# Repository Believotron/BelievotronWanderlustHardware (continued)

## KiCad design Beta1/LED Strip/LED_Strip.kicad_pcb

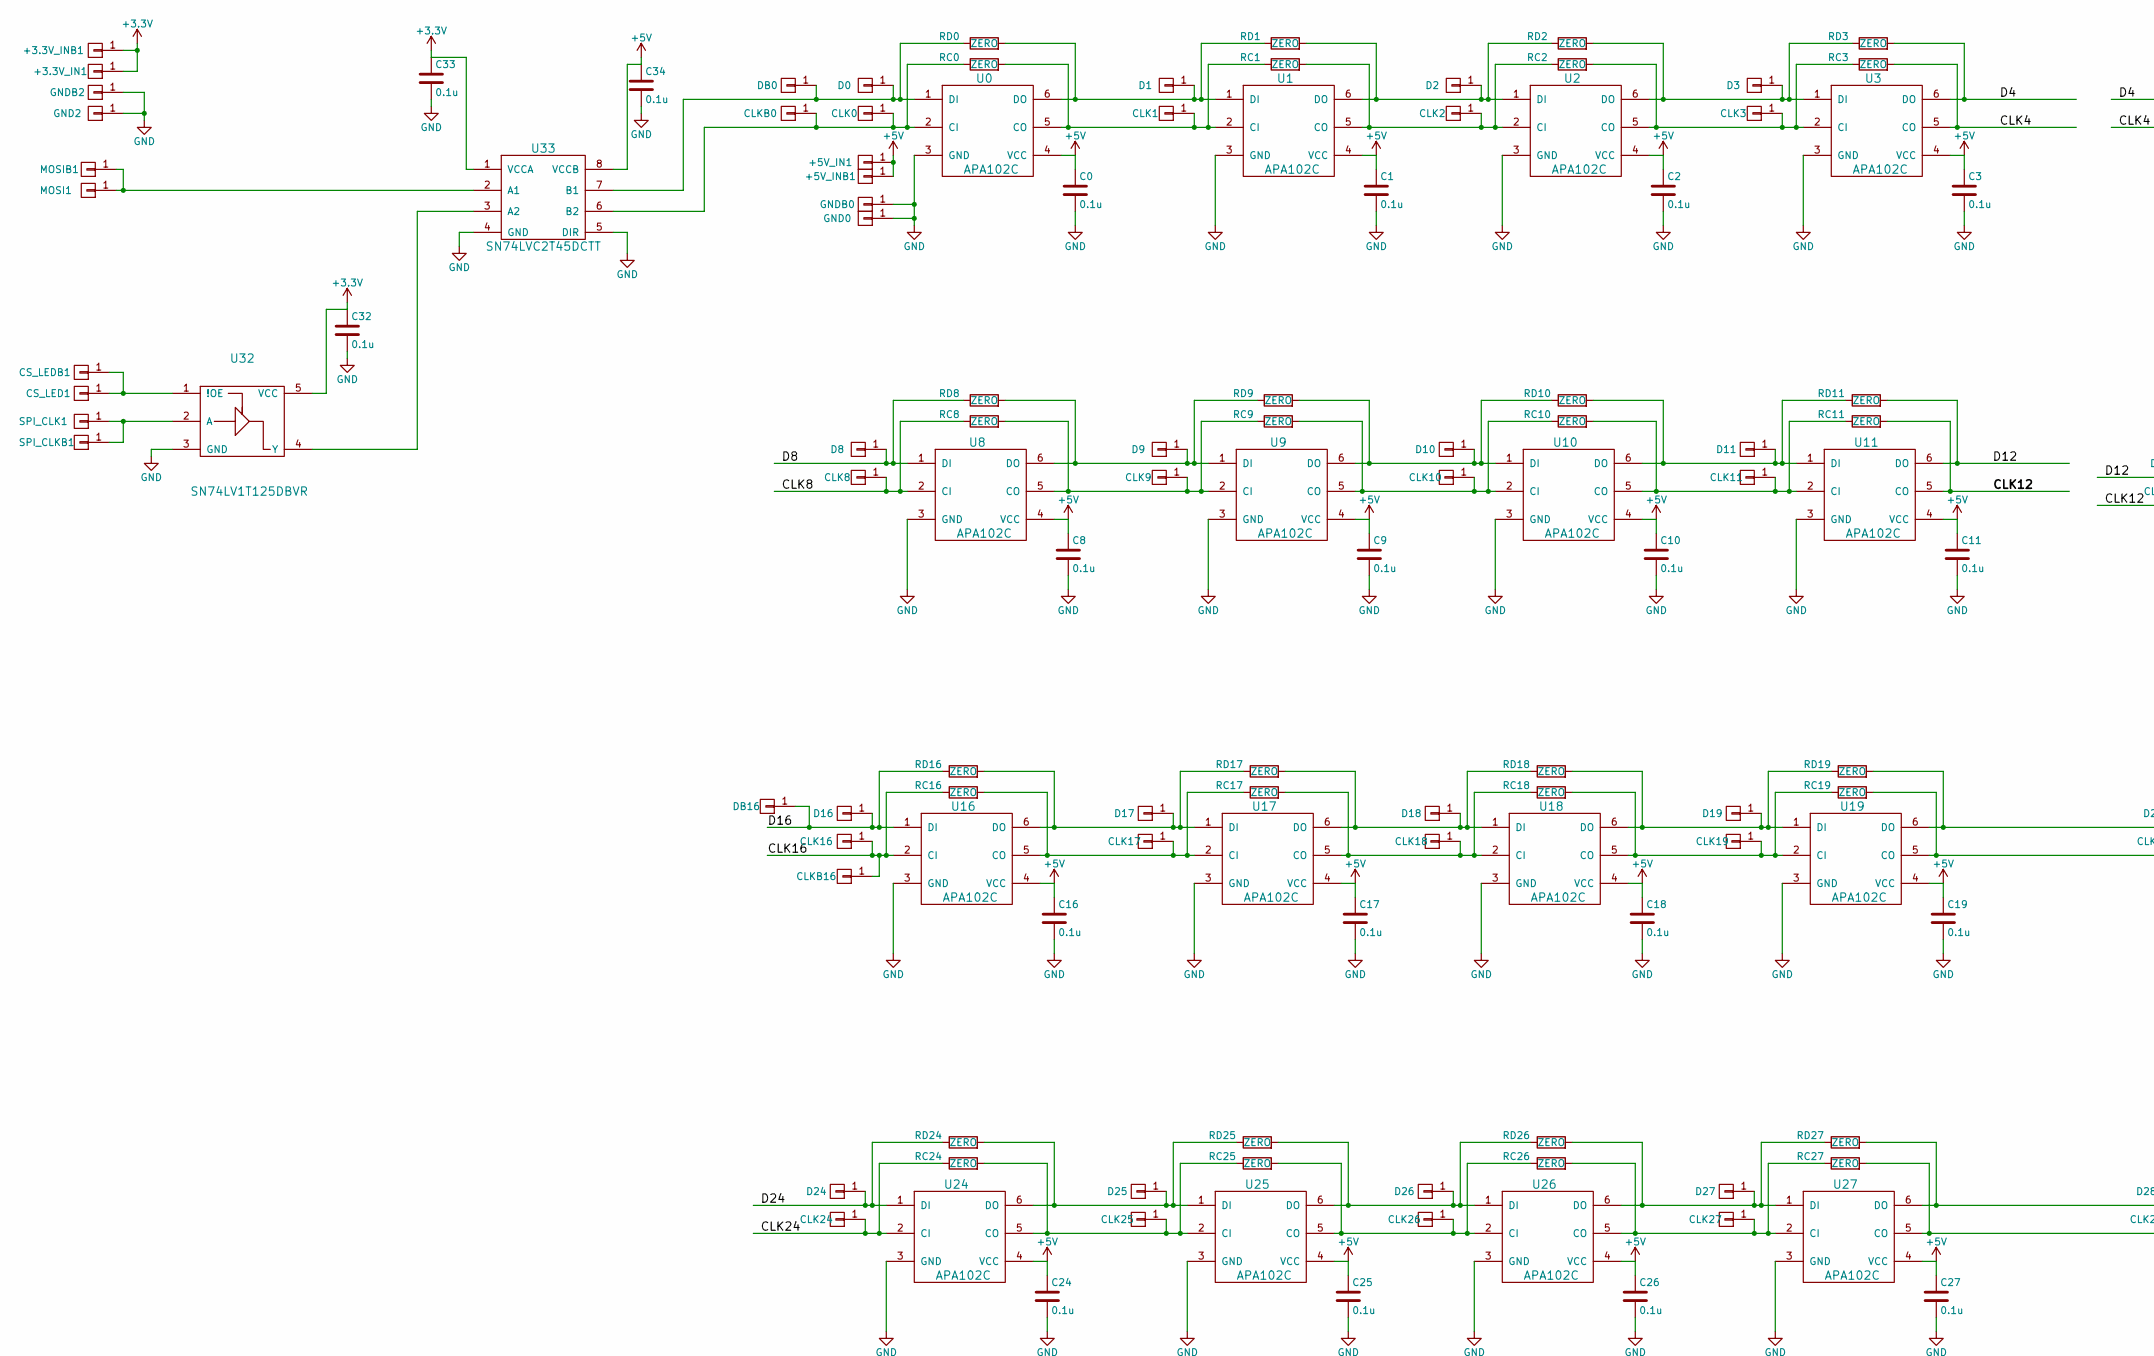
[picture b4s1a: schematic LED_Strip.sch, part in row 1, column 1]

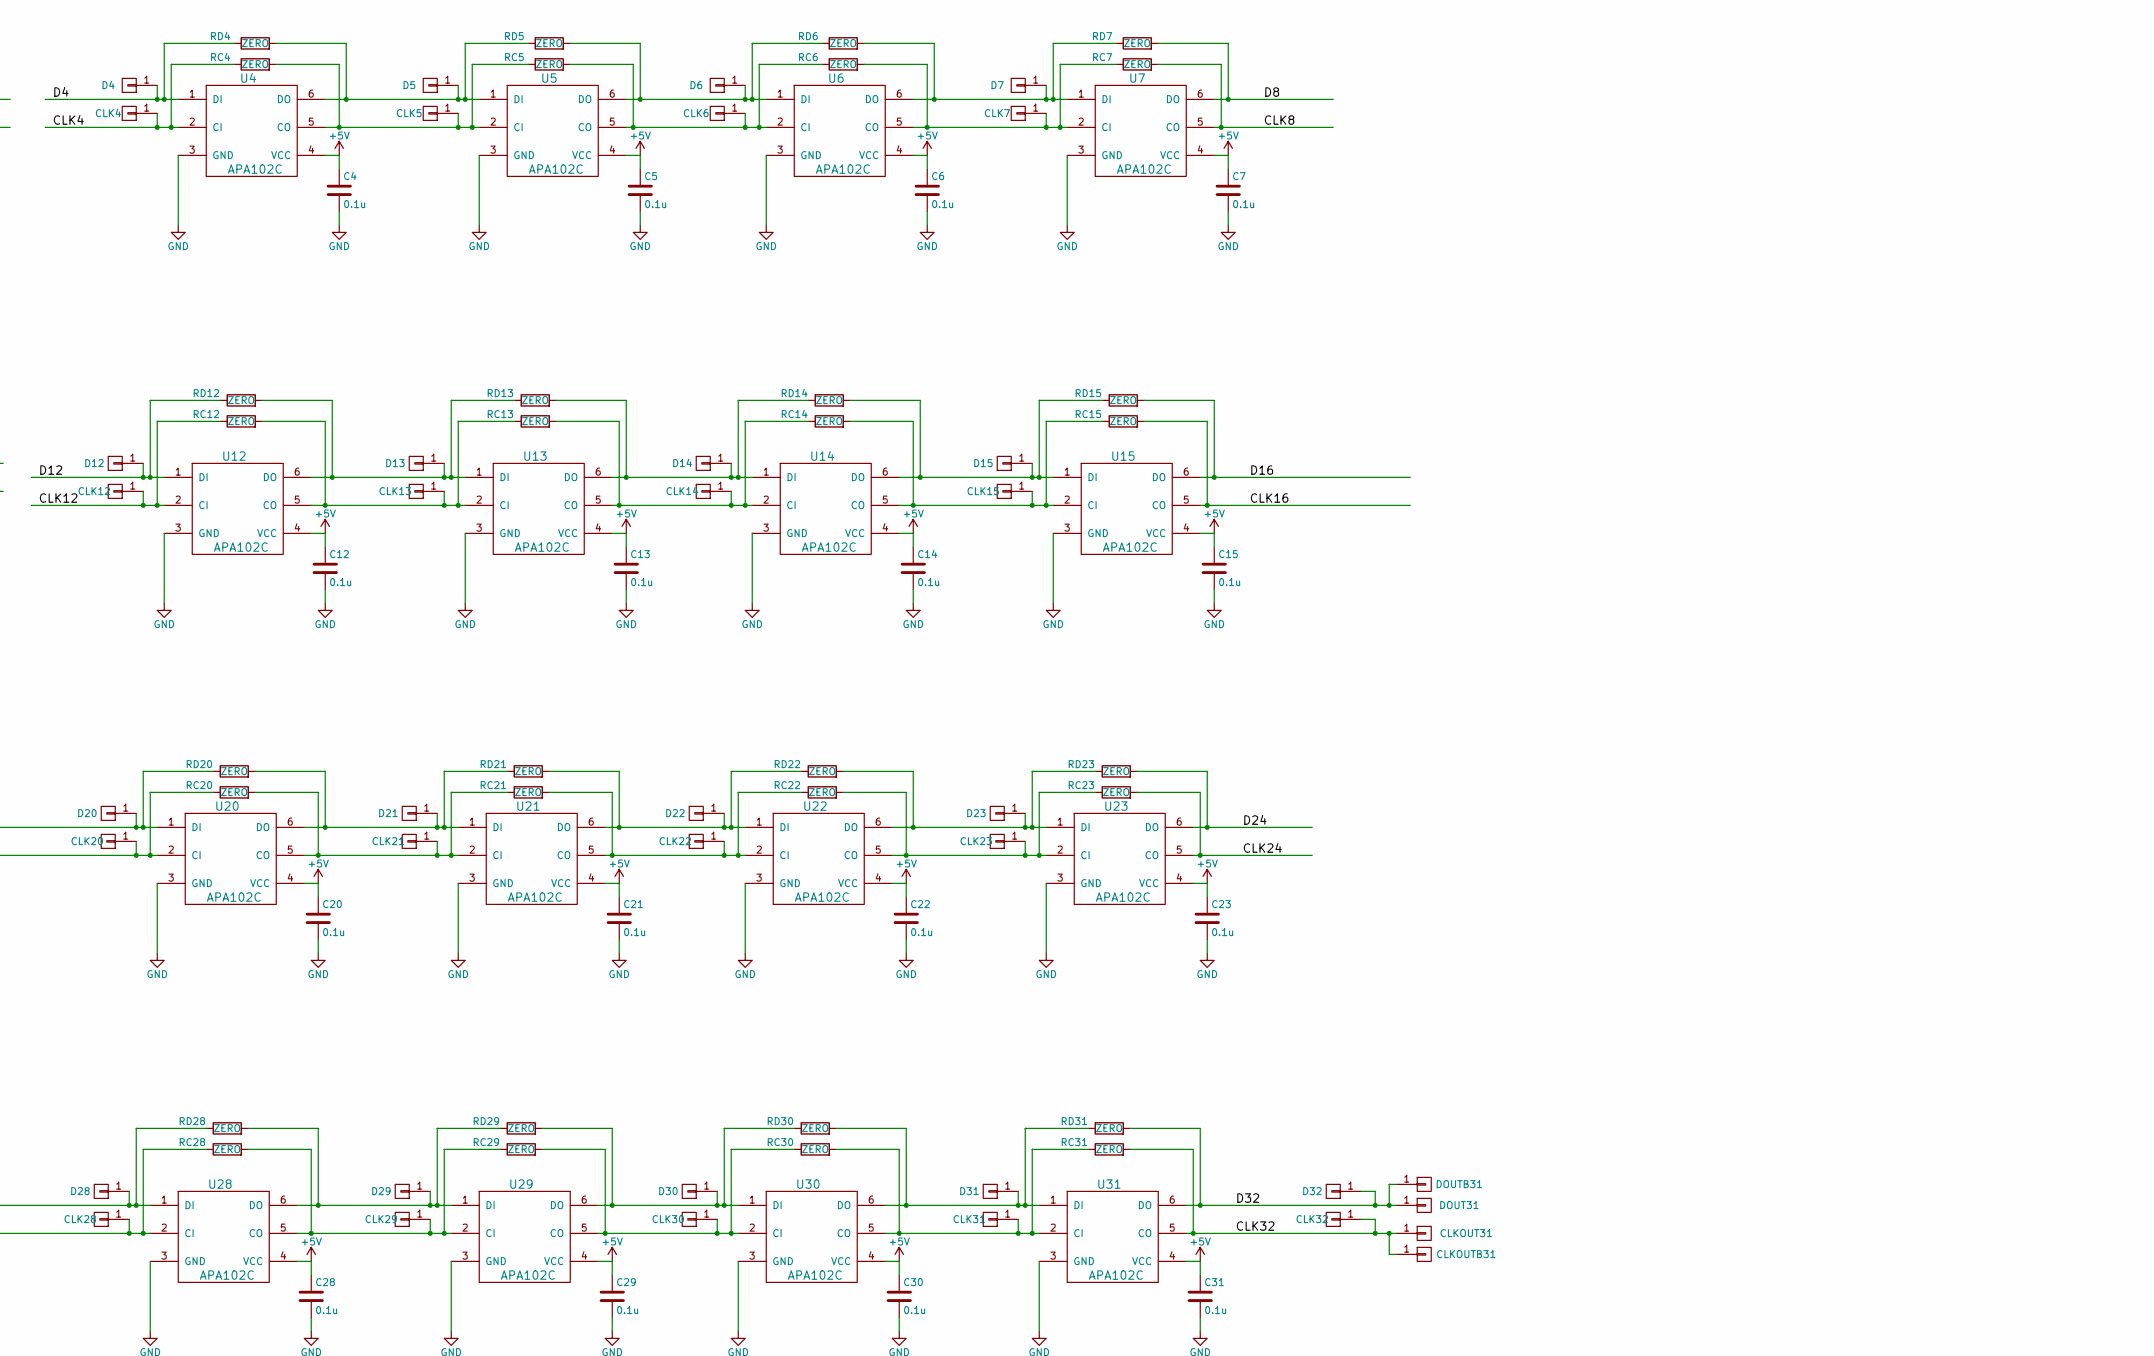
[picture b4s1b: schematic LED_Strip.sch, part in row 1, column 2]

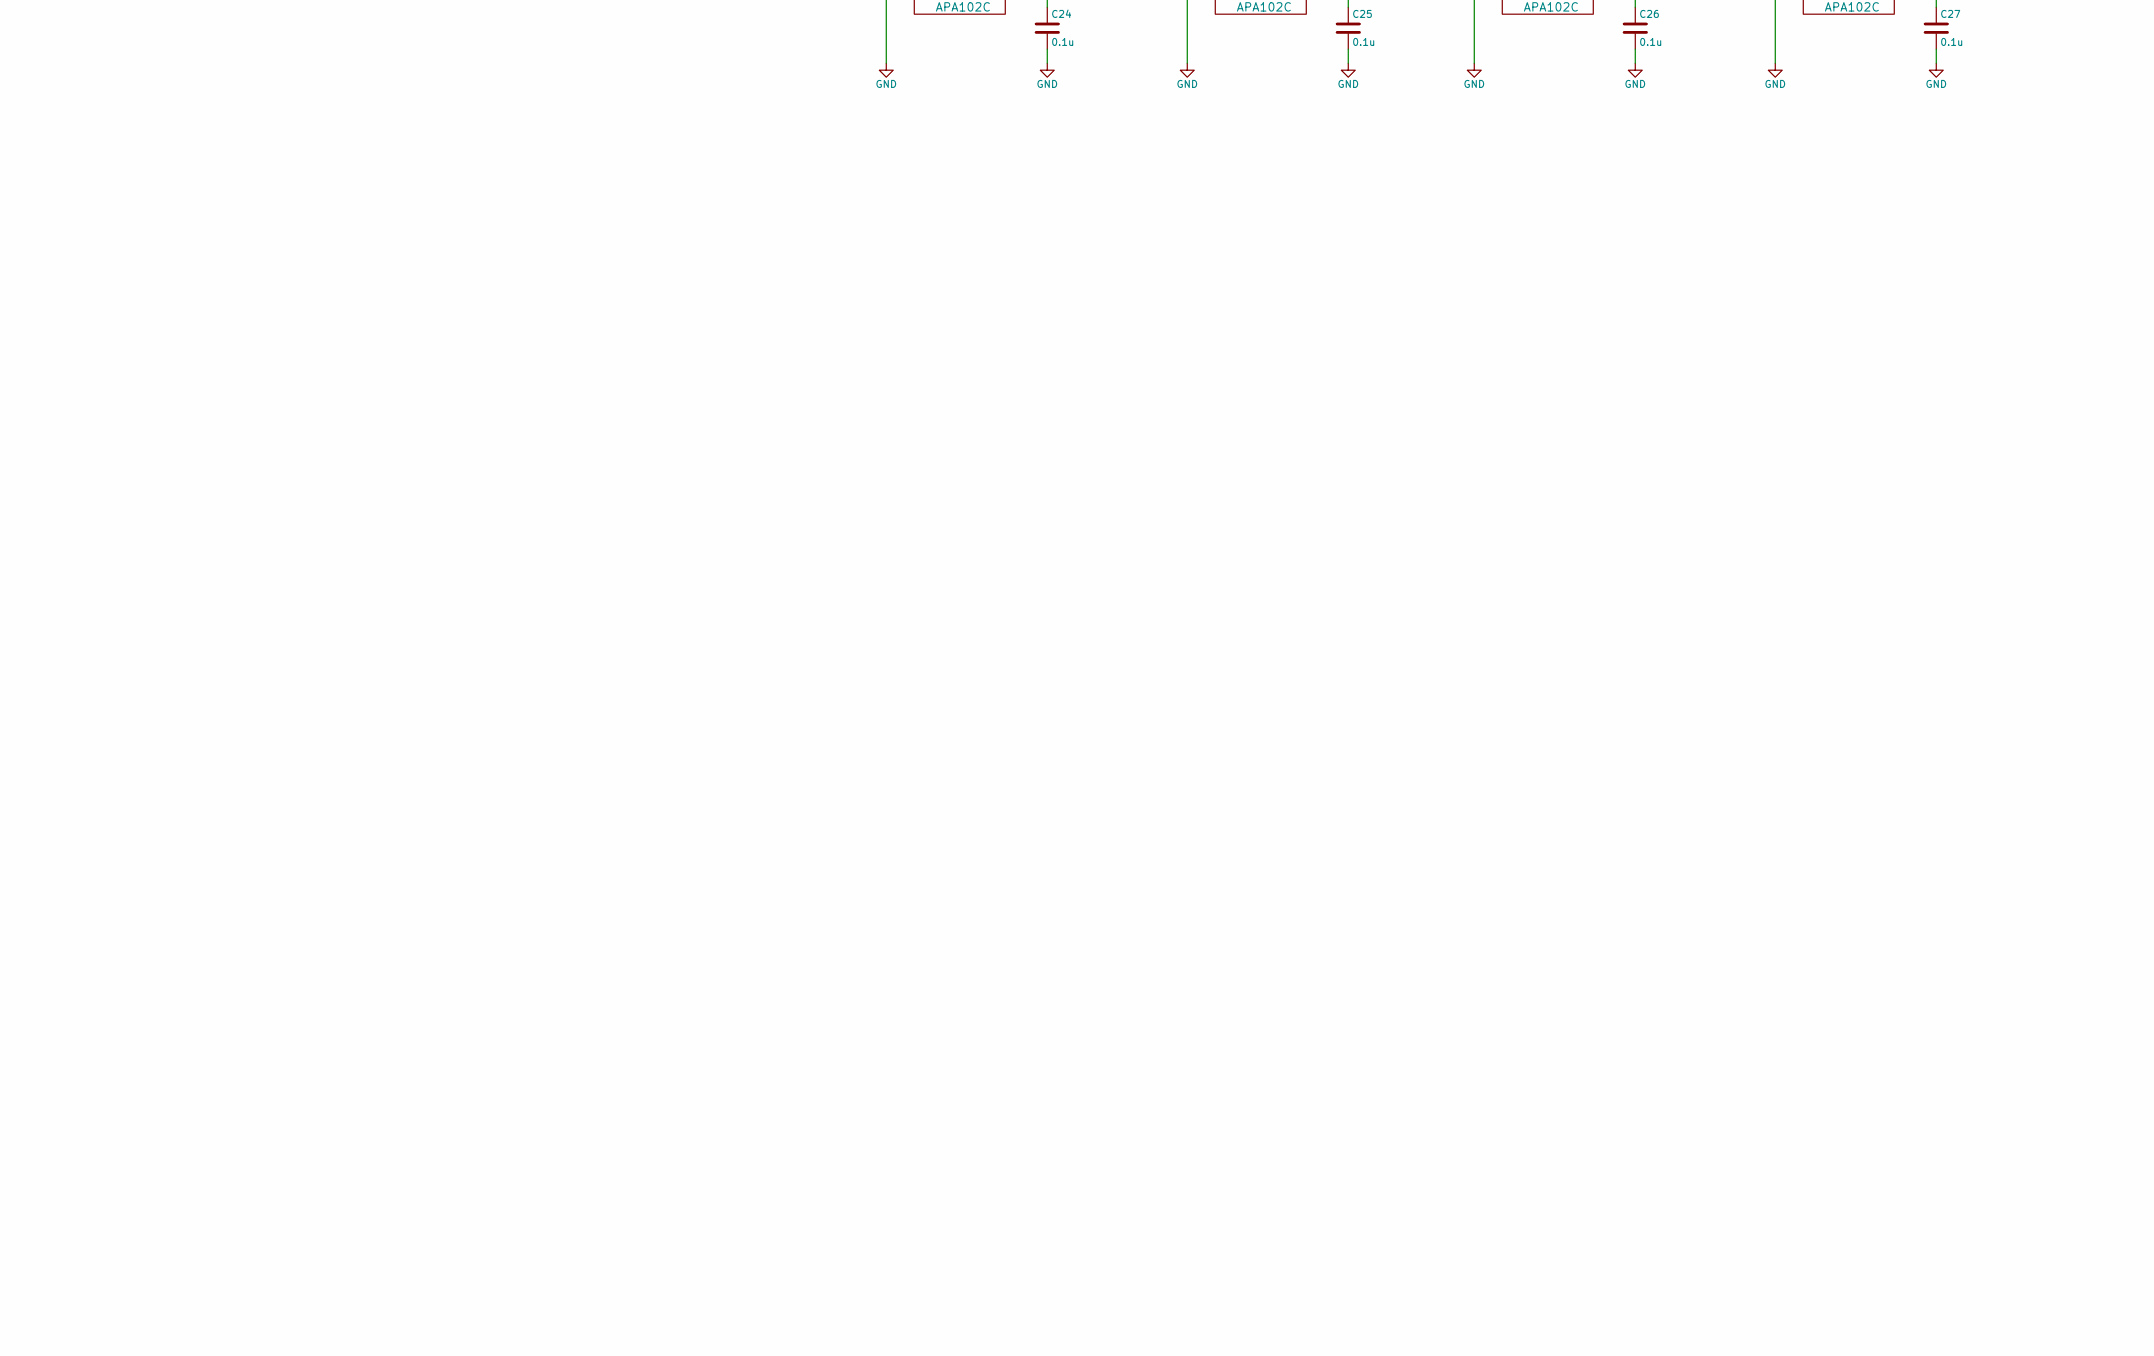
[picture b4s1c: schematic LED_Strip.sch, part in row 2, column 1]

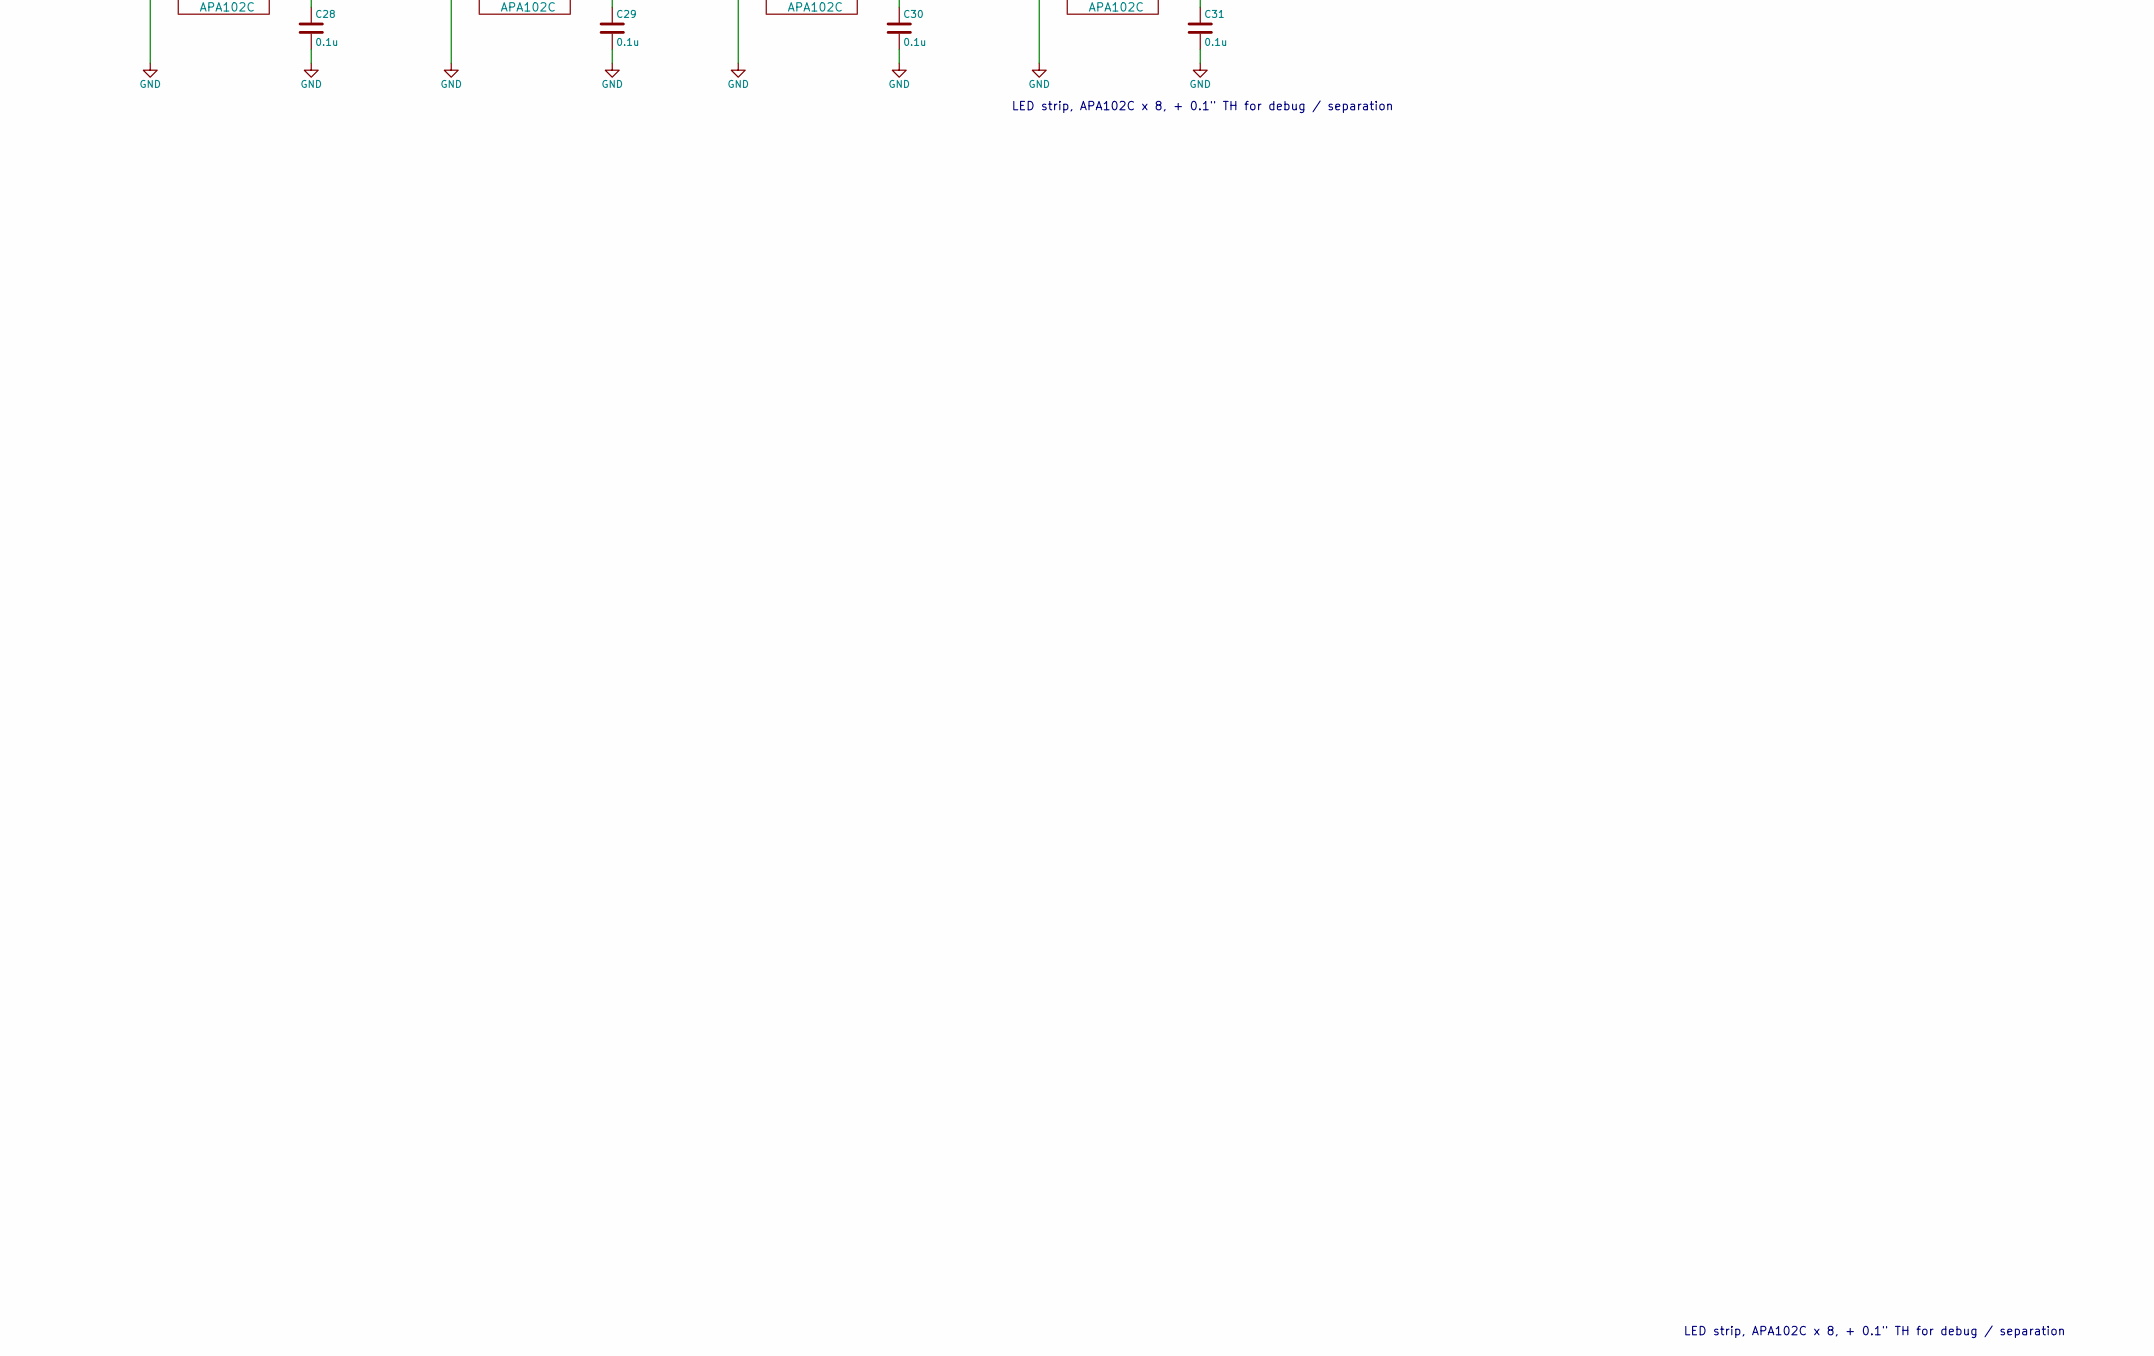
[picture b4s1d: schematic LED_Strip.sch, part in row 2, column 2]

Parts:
+3.3V_IN1, +3.3V_INB1, +5V_IN1, +5V_INB1: CONN_01X01; single_0.1; MPN ON_PCB
C0, C1, C2, C3, C4, C5, C6, C7, C8, C9, C10, C11, C12, C13, C14, C15, C16, C17, C18, C19, C20, C21, C22, C23, C24, C25, C26, C27, C28, C29, C30, C31, C32, C33, C34: 0.1u; C_0603; MPN CC0603KRX7R9BB104
CLK0, CLK16: CONN_01X01; single_0.1; MPN ON_PCB
CLK1, CLK2, CLK3, CLK4, CLK5, CLK6, CLK7, CLK8, CLK9, CLK10, CLK11, CLK12, CLK13, CLK14, CLK15, CLK17, CLK18, CLK19, CLK20, CLK21, CLK22, CLK23, CLK24, CLK25, CLK26, CLK27, CLK28, CLK29, CLK30, CLK31, CLK32: CONN_01X01; TESTPAD; MPN ON_PCB
CLKB0, CLKB16: CONN_01X01; single_0.1; MPN ON_PCB
CLKOUT31: CONN_01X01; single_0.1; MPN ON_PCB
CLKOUTB31: CONN_01X01; single_0.1; MPN ON_PCB
CS_LED1: CONN_01X01; single_0.1; MPN ON_PCB
CS_LEDB1: CONN_01X01; single_0.1; MPN ON_PCB
D0, D16: CONN_01X01; single_0.1; MPN ON_PCB
D1, D2, D3, D4, D5, D6, D7, D8, D9, D10, D11, D12, D13, D14, D15, D17, D18, D19, D20, D21, D22, D23, D24, D25, D26, D27, D28, D29, D30, D31, D32: CONN_01X01; TESTPAD; MPN ON_PCB
DB0, DB16: CONN_01X01; single_0.1; MPN ON_PCB
DOUT31: CONN_01X01; single_0.1; MPN ON_PCB
DOUTB31: CONN_01X01; single_0.1; MPN ON_PCB
GND0, GND2: CONN_01X01; single_0.1; MPN ON_PCB
GNDB0, GNDB2: CONN_01X01; single_0.1; MPN ON_PCB
MOSI1: CONN_01X01; single_0.1; MPN ON_PCB
MOSIB1: CONN_01X01; single_0.1; MPN ON_PCB
RC0, RC1, RC2, RC3, RC4, RC5, RC6, RC7, RC8, RC9, RC10, RC11, RC12, RC13, RC14, RC15, RC16, RC17, RC18, RC19, RC20, RC21, RC22, RC23, RC24, RC25, RC26, RC27, RC28, RC29, RC30, RC31: ZERO; R_0603; MPN CRCW06030000Z0EA
RD0, RD1, RD2, RD3, RD4, RD5, RD6, RD7, RD8, RD9, RD10, RD11, RD12, RD13, RD14, RD15, RD16, RD17, RD18, RD19, RD20, RD21, RD22, RD23, RD24, RD25, RD26, RD27, RD28, RD29, RD30, RD31: ZERO; R_0603; MPN CRCW06030000Z0EA
SPI_CLK1: CONN_01X01; single_0.1; MPN ON_PCB
SPI_CLKB1: CONN_01X01; single_0.1; MPN ON_PCB
U0, U1, U2, U3, U4, U5, U6, U7, U8, U9, U10, U11, U12, U13, U14, U15, U16, U17, U18, U19, U20, U21, U22, U23, U24, U25, U26, U27, U28, U29, U30, U31: APA102C; PLCC6-1.6x4.2_LED; MPN APA102C
U32: SN74LV1T125DBVR; SOT23-5; MPN SN74LV1T125DBVR
U33: SN74LVC2T45DCTT; SSOP8; MPN SN74LVC2T45DCTT

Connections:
+3V3: +3.3V_IN1.1, +3.3V_INB1.1, C32.1, C33.1, U32.5 (VCC), U33.1 (VCCA)
+5V: +5V_IN1.1, +5V_INB1.1, C0.1, C1.1, C2.1, C3.1, C4.1, C5.1, C6.1, C7.1, C8.1, C9.1, C10.1, C11.1, C12.1, C13.1, C14.1, C15.1, C16.1, C17.1, C18.1, C19.1, C20.1, C21.1, C22.1, C23.1, C24.1, C25.1, C26.1, C27.1, C28.1, C29.1, C30.1, C31.1, C34.1, U0.4 (VCC), U1.4 (VCC), U2.4 (VCC), U3.4 (VCC), U4.4 (VCC), U5.4 (VCC), U6.4 (VCC), U7.4 (VCC), U8.4 (VCC), U9.4 (VCC), U10.4 (VCC), U11.4 (VCC), U12.4 (VCC), U13.4 (VCC), U14.4 (VCC), U15.4 (VCC), U16.4 (VCC), U17.4 (VCC), U18.4 (VCC), U19.4 (VCC), U20.4 (VCC), U21.4 (VCC), U22.4 (VCC), U23.4 (VCC), U24.4 (VCC), U25.4 (VCC), U26.4 (VCC), U27.4 (VCC), U28.4 (VCC), U29.4 (VCC), U30.4 (VCC), U31.4 (VCC), U33.8 (VCCB); also elsewhere on the board
/CLK: CLK0.1, CLKB0.1, RC0.1, U0.2 (CI), U33.6 (B2); also elsewhere on the board
/CLK4: CLK4.1, RC3.2, RC4.1, U3.5 (CO), U4.2 (CI)
/CLK8: CLK8.1, RC7.2, RC8.1, U7.5 (CO), U8.2 (CI)
/CLK12: CLK12.1, RC11.2, RC12.1, U11.5 (CO), U12.2 (CI)
/CLK16: CLK16.1, CLKB16.1, RC15.2, RC16.1, U15.5 (CO), U16.2 (CI)
/CLK24: CLK24.1, RC23.2, RC24.1, U23.5 (CO), U24.2 (CI)
/CLK32: CLK32.1, CLKOUT31.1, CLKOUTB31.1, RC31.2, U31.5 (CO)
/D4: D4.1, RD3.2, RD4.1, U3.6 (DO), U4.1 (DI)
/D8: D8.1, RD7.2, RD8.1, U7.6 (DO), U8.1 (DI)
/D12: D12.1, RD11.2, RD12.1, U11.6 (DO), U12.1 (DI)
/D16: D16.1, DB16.1, RD15.2, RD16.1, U15.6 (DO), U16.1 (DI)
/D24: D24.1, RD23.2, RD24.1, U23.6 (DO), U24.1 (DI)
/D32: D32.1, DOUT31.1, DOUTB31.1, RD31.2, U31.6 (DO)
/Data: D0.1, DB0.1, RD0.1, U0.1 (DI), U33.7 (B1); also elsewhere on the board
GND: C0.2, C1.2, C2.2, C3.2, C4.2, C5.2, C6.2, C7.2, C8.2, C9.2, C10.2, C11.2, C12.2, C13.2, C14.2, C15.2, C16.2, C17.2, C18.2, C19.2, C20.2, C21.2, C22.2, C23.2, C24.2, C25.2, C26.2, C27.2, C28.2, C29.2, C30.2, C31.2, C32.2, C33.2, C34.2, GND0.1, GND2.1, GNDB0.1, GNDB2.1, U0.3 (GND), U1.3 (GND), U2.3 (GND), U3.3 (GND), U4.3 (GND), U5.3 (GND), U6.3 (GND), U7.3 (GND), U8.3 (GND), U9.3 (GND), U10.3 (GND), U11.3 (GND), U12.3 (GND), U13.3 (GND), U14.3 (GND), U15.3 (GND), U16.3 (GND), U17.3 (GND), U18.3 (GND), U19.3 (GND), U20.3 (GND), U21.3 (GND), U22.3 (GND), U23.3 (GND), U24.3 (GND), U25.3 (GND), U26.3 (GND), U27.3 (GND), U28.3 (GND), U29.3 (GND), U30.3 (GND), U31.3 (GND), U32.3 (GND), U33.4 (GND), U33.5 (DIR); also elsewhere on the board
unnamed: CLK1.1, RC0.2, RC1.1, U0.5 (CO), U1.2 (CI)
unnamed: CLK2.1, RC1.2, RC2.1, U1.5 (CO), U2.2 (CI)
unnamed: CLK3.1, RC2.2, RC3.1, U2.5 (CO), U3.2 (CI)
unnamed: CLK5.1, RC4.2, RC5.1, U4.5 (CO), U5.2 (CI)
unnamed: CLK6.1, RC5.2, RC6.1, U5.5 (CO), U6.2 (CI)
unnamed: CLK7.1, RC6.2, RC7.1, U6.5 (CO), U7.2 (CI)
unnamed: CLK9.1, RC8.2, RC9.1, U8.5 (CO), U9.2 (CI)
unnamed: CLK10.1, RC9.2, RC10.1, U9.5 (CO), U10.2 (CI)
unnamed: CLK11.1, RC10.2, RC11.1, U10.5 (CO), U11.2 (CI)
unnamed: CLK13.1, RC12.2, RC13.1, U12.5 (CO), U13.2 (CI)
unnamed: CLK14.1, RC13.2, RC14.1, U13.5 (CO), U14.2 (CI)
unnamed: CLK15.1, RC14.2, RC15.1, U14.5 (CO), U15.2 (CI)
unnamed: CLK17.1, RC16.2, RC17.1, U16.5 (CO), U17.2 (CI)
unnamed: CLK18.1, RC17.2, RC18.1, U17.5 (CO), U18.2 (CI)
unnamed: CLK19.1, RC18.2, RC19.1, U18.5 (CO), U19.2 (CI)
unnamed: CLK20.1, RC19.2, RC20.1, U19.5 (CO), U20.2 (CI)
unnamed: CLK21.1, RC20.2, RC21.1, U20.5 (CO), U21.2 (CI)
unnamed: CLK22.1, RC21.2, RC22.1, U21.5 (CO), U22.2 (CI)
unnamed: CLK23.1, RC22.2, RC23.1, U22.5 (CO), U23.2 (CI)
unnamed: CLK25.1, RC24.2, RC25.1, U24.5 (CO), U25.2 (CI)
unnamed: CLK26.1, RC25.2, RC26.1, U25.5 (CO), U26.2 (CI)
unnamed: CLK27.1, RC26.2, RC27.1, U26.5 (CO), U27.2 (CI)
unnamed: CLK28.1, RC27.2, RC28.1, U27.5 (CO), U28.2 (CI)
unnamed: CLK29.1, RC28.2, RC29.1, U28.5 (CO), U29.2 (CI)
unnamed: CLK30.1, RC29.2, RC30.1, U29.5 (CO), U30.2 (CI)
unnamed: CLK31.1, RC30.2, RC31.1, U30.5 (CO), U31.2 (CI)
unnamed 43: CS_LED1.1, CS_LEDB1.1, U32.1 (!OE); also elsewhere on the board
unnamed: D1.1, RD0.2, RD1.1, U0.6 (DO), U1.1 (DI)
unnamed: D2.1, RD1.2, RD2.1, U1.6 (DO), U2.1 (DI)
unnamed: D3.1, RD2.2, RD3.1, U2.6 (DO), U3.1 (DI)
unnamed: D5.1, RD4.2, RD5.1, U4.6 (DO), U5.1 (DI)
unnamed: D6.1, RD5.2, RD6.1, U5.6 (DO), U6.1 (DI)
unnamed: D7.1, RD6.2, RD7.1, U6.6 (DO), U7.1 (DI)
unnamed: D9.1, RD8.2, RD9.1, U8.6 (DO), U9.1 (DI)
unnamed: D10.1, RD9.2, RD10.1, U9.6 (DO), U10.1 (DI)
unnamed: D11.1, RD10.2, RD11.1, U10.6 (DO), U11.1 (DI)
unnamed: D13.1, RD12.2, RD13.1, U12.6 (DO), U13.1 (DI)
unnamed: D14.1, RD13.2, RD14.1, U13.6 (DO), U14.1 (DI)
unnamed: D15.1, RD14.2, RD15.1, U14.6 (DO), U15.1 (DI)
unnamed: D17.1, RD16.2, RD17.1, U16.6 (DO), U17.1 (DI)
unnamed: D18.1, RD17.2, RD18.1, U17.6 (DO), U18.1 (DI)
unnamed: D19.1, RD18.2, RD19.1, U18.6 (DO), U19.1 (DI)
unnamed: D20.1, RD19.2, RD20.1, U19.6 (DO), U20.1 (DI)
unnamed: D21.1, RD20.2, RD21.1, U20.6 (DO), U21.1 (DI)
unnamed: D22.1, RD21.2, RD22.1, U21.6 (DO), U22.1 (DI)
unnamed: D23.1, RD22.2, RD23.1, U22.6 (DO), U23.1 (DI)
unnamed: D25.1, RD24.2, RD25.1, U24.6 (DO), U25.1 (DI)
unnamed: D26.1, RD25.2, RD26.1, U25.6 (DO), U26.1 (DI)
unnamed: D27.1, RD26.2, RD27.1, U26.6 (DO), U27.1 (DI)
unnamed: D28.1, RD27.2, RD28.1, U27.6 (DO), U28.1 (DI)
unnamed: D29.1, RD28.2, RD29.1, U28.6 (DO), U29.1 (DI)
unnamed: D30.1, RD29.2, RD30.1, U29.6 (DO), U30.1 (DI)
unnamed: D31.1, RD30.2, RD31.1, U30.6 (DO), U31.1 (DI)
unnamed 70: MOSI1.1, MOSIB1.1, U33.2 (A1); also elsewhere on the board
unnamed 71: SPI_CLK1.1, SPI_CLKB1.1, U32.2 (A); also elsewhere on the board
unnamed: U32.4 (Y), U33.3 (A2)

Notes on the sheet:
LED strip, APA102C x 8, + 0.1" TH for debug / separation

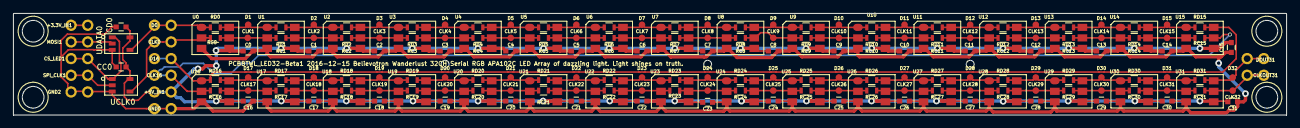
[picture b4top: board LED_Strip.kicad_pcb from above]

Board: 2 copper layers, 194.0 x 15.5 mm, 220 parts (0 on the bottom side), 72 nets.

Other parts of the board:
CC0: 0.1u; C_0603
CD0: 0.1u; C_0603
UCLK0: SN74LV1T125DBVR; SOT23-5
UDATA0: SN74LV1T125DBVR; SOT23-5

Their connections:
+5V: CC0.1, CD0.1, UCLK0.5, UDATA0.5; also elsewhere on the board
/CLK: UCLK0.4; also elsewhere on the board
/Data: UDATA0.4; also elsewhere on the board
GND: CC0.2, CD0.2, UCLK0.3, UDATA0.3; also elsewhere on the board
unnamed 43: UCLK0.1, UDATA0.1; also elsewhere on the board
unnamed 70: UDATA0.2; also elsewhere on the board
unnamed 71: UCLK0.2; also elsewhere on the board

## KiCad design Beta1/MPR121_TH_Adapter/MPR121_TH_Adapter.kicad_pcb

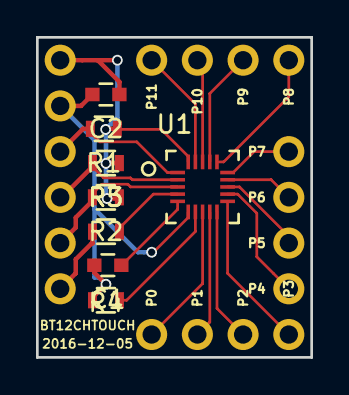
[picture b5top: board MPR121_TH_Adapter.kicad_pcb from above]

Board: 2 copper layers, 15.2 x 17.8 mm, 26 parts (0 on the bottom side), 21 nets.

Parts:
+3V3: CONN_01X01; single_0.1
ADDR1: CONN_01X01; single_0.1
C1: 0.1uf; C_0603
C2: CC0603KRX7R9BB104; C_0603
GND1: CONN_01X01; single_0.1
IRQ1: CONN_01X01; single_0.1
P0, P1, P2, P3, P4, P5, P6, P7, P8, P9, P10, P11: CONN_01X01; single_0.1
R1, R2, R5: 10K; R_0603
R3: 100K; R_0603
R4: 75K; R_0603
SCL1: CONN_01X01; single_0.1
SDA1: CONN_01X01; single_0.1
U1: MPR121QR2; QFN-20-1EP_3x3mm_Pitch0.40mm

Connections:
+3V3: +3V3.1, C2.1, R1.1, R2.1, R5.1, U1.20
/IRQ: IRQ1.1, R1.2, U1.1
/P00: P0.1, U1.8
/P01: P1.1, U1.9
/P02: P2.1, U1.10
/P03: P3.1, U1.11
/P04: P4.1, U1.12
/P05: P5.1, U1.13
/P06: P6.1, U1.14
/P07: P7.1, U1.15
/P08: P8.1, U1.16
/P09: P9.1, U1.17
/P10: P10.1, U1.18
/P11: P11.1, U1.19
/SCL: R5.2, SCL1.1, U1.2
/SDA: R2.2, SDA1.1, U1.3
GND: C1.2, C2.2, GND1.1, R4.2, U1.6
unnamed: ADDR1.1, R3.1
unnamed: C1.1, U1.5
unnamed: R3.2, U1.4
unnamed: R4.1, U1.7
